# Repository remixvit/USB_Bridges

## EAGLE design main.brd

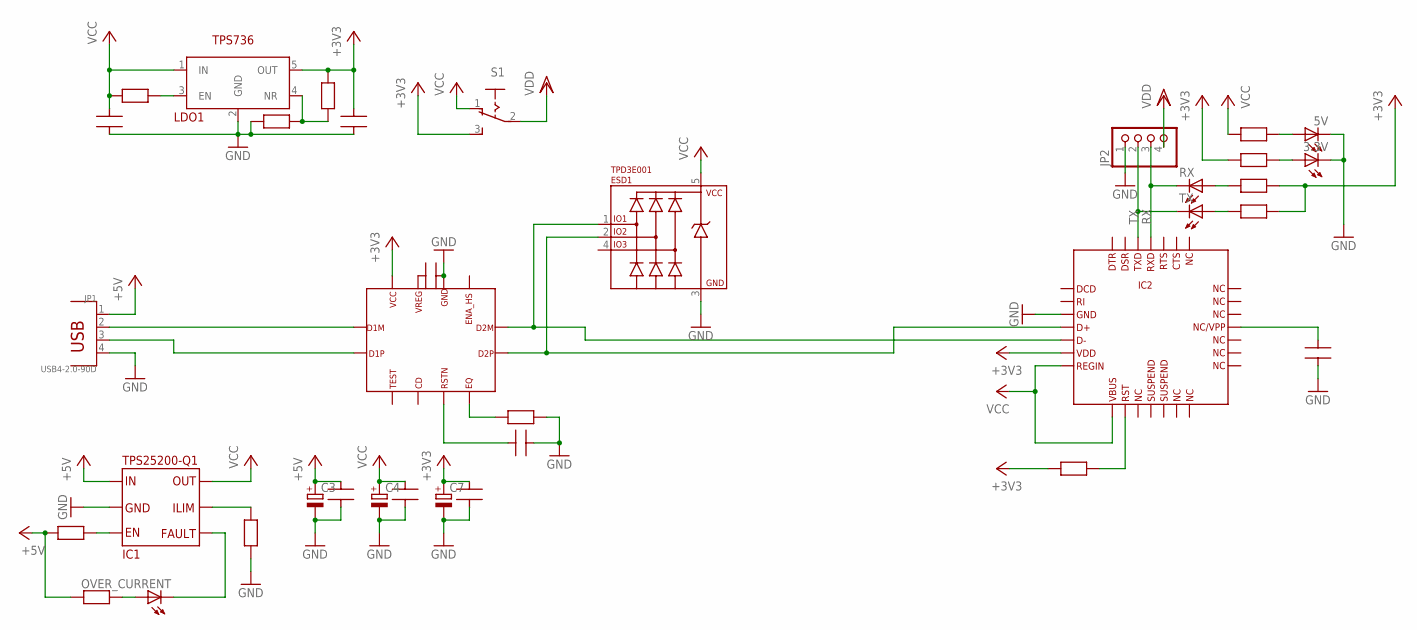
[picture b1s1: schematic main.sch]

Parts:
3.3V, 5V: LEDCHIP-LED0603; CHIP-LED0603
C1, C2, C5, C6, C8, C9, C10, C11: CAP0603; C0603
C3, C4, C7: CPOL-EUSMCA; SMC_A
ESD1: TPD3E001; SOT23-5
IC1: TPS25200-Q1; PWSON6
IC2: CP2102/9; QFN-28
JP1: USB4-2.0-90D; USB4+2P-2.0-90D
JP2: PINHD-1X4; 1X04
LDO1: TPS736; SOT23-5
OVER_CURRENT: LEDCHIP-LED0603; CHIP-LED0603
R1, R2, R3, R4, R5, R6, R7, R8, R9, R10, R11, R12: RES0603; R0603
RX: LEDCHIP-LED0603; CHIP-LED0603
S1: 255SB
TX: LEDCHIP-LED0603; CHIP-LED0603
USB1: TUSB211QRWBRQ1; X2QFN

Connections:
+3V3: C2.2, C7.+, C8.2, IC2.6, LDO1.5 (OUT), R2.1, R7.1, R8.2, R9.2, R10.1, S1.3 (S), USB1.12
+5V: C3.+, C5.2, IC1.P$1, JP1.1, R4.2, R12.1
GND: 3.3V.C, 5V.C, C1.1, C2.1, C3.-, C4.-, C5.1, C6.1, C7.-, C8.1, C9.1, C10.1, C11.2, ESD1.3, IC1.EPAD, IC1.P$2, IC2.3, IC2.EPAD_B, IC2.EPAD_T, IC2.EPAD_VIA1, IC2.EPAD_VIA2, IC2.EPAD_VIA3, IC2.EPAD_VIA4, IC2.EPAD_VIA5, IC2.EPAD_VIA6, IC2.EPAD_VIA7, IC2.EPAD_VIA8, IC2.EPAD_VIA9, JP1.4, JP2.1, LDO1.2 (GND), R3.1, R5.2, R6.2, USB1.10
unnamed: JP1.2, USB1.1
unnamed: JP1.3, USB1.2
unnamed: LDO1.3 (EN), R1.1
unnamed: LDO1.4 (NR), R2.2, R3.2
unnamed: IC1.P$3, R4.1
unnamed: IC1.P$5, R5.1
unnamed: ESD1.1, IC2.5, USB1.8
unnamed: ESD1.2, IC2.4, USB1.7
unnamed: C9.2, USB1.11
unnamed: R6.1, USB1.6
unnamed: C10.2, USB1.5
unnamed: IC2.9, R7.2
unnamed: R8.1, RX.A
unnamed: R9.1, TX.A
unnamed: C11.1, IC2.18
unnamed: 3.3V.A, R10.2
unnamed: OVER_CURRENT.A, R12.2
unnamed: IC1.P$4, OVER_CURRENT.C
unnamed: 5V.A, R11.2
RX: IC2.25, JP2.3, RX.C
TX: IC2.26, JP2.2, TX.C
VCC: C1.2, C4.+, C6.2, ESD1.5, IC1.P$6, IC2.7, IC2.8, LDO1.1 (IN), R1.2, R11.1, S1.1 (O)
VDD: JP2.4, S1.2

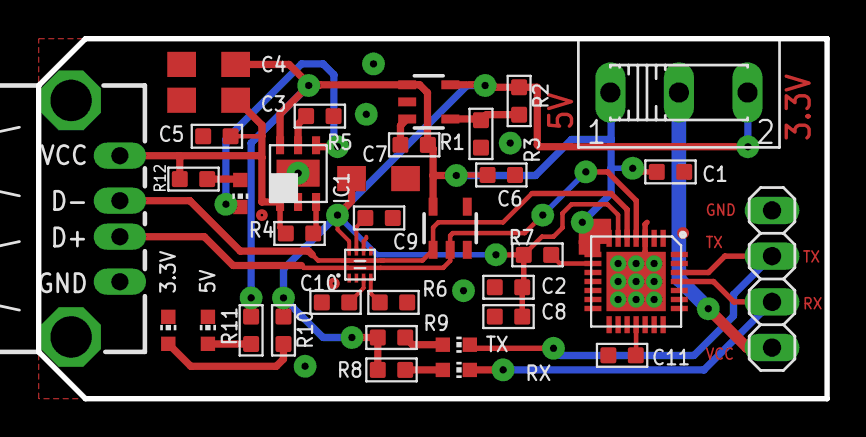
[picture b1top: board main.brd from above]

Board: 2 copper layers, 43.8 x 20.0 mm, 36 parts (0 on the bottom side), 26 nets.

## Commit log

2016-03-02 Create PCB
